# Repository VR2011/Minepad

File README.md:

A macropad to play Minecraft with!

# Features
Not much; it has 11 keys that are binded to the following keys: Esc, F3, E, Q, T, W, A, S, D, Space, Tab

# Schematic

# PCB

# CAD

# Bill of Materials
- 4x M3x5mx4mm heatset inserts
- 1x Seeedxiao RP2040 Microcontroller
- 11x MX-Style Switches
- 4x M3x16mm SHCS Bolt
- 11x White blank DSA keycaps
- 1x PCB
- 2x 3D Printed Case (Top and Bottom Parts)

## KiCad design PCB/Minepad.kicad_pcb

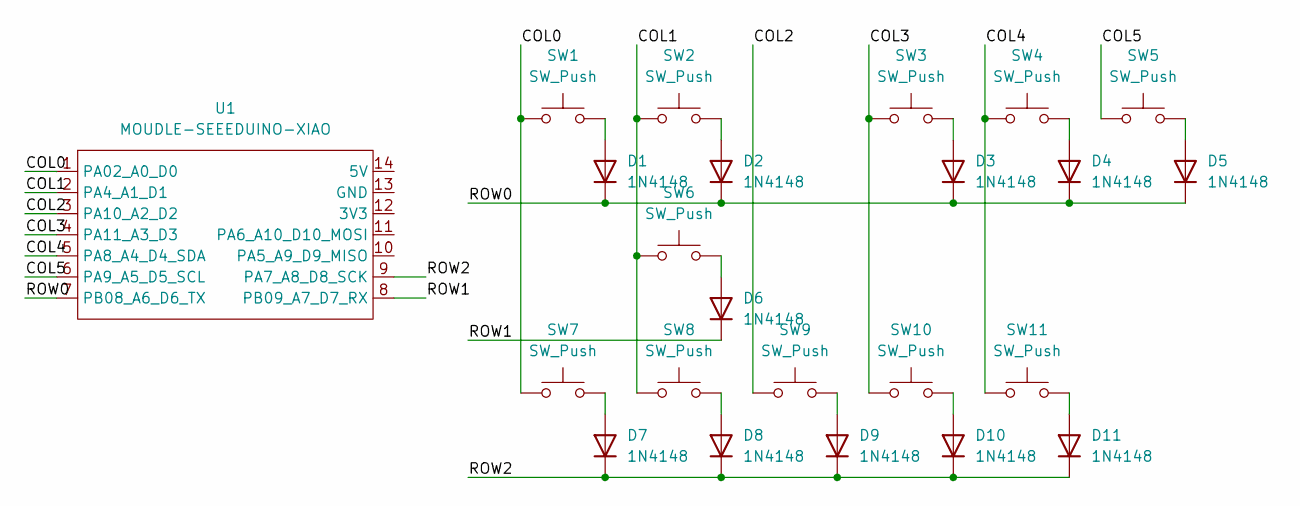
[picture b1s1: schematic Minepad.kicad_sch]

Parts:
D1, D2, D3, D4, D5, D6, D7, D8, D9, D10, D11: 1N4148; D_DO-35_SOD27_P7.62mm_Horizontal
SW1, SW2, SW3, SW4, SW5, SW6, SW7, SW8, SW9, SW10, SW11: SW_Push; SW_Cherry_MX_1.00u_PCB
U1: MOUDLE-SEEEDUINO-XIAO; XIAO-Generic-Hybrid-14P-2.54-21X17.8MM

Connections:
/COL0: SW1.1, SW7.1, U1.1 (PA02_A0_D0)
/COL1: SW2.1, SW6.1, SW8.1, U1.2 (PA4_A1_D1)
/COL2: SW9.1, U1.3 (PA10_A2_D2)
/COL3: SW3.1, SW10.1, U1.4 (PA11_A3_D3)
/COL4: SW4.1, SW11.1, U1.5 (PA8_A4_D4_SDA)
/COL5: SW5.1, U1.6 (PA9_A5_D5_SCL)
/ROW0: D1.1 (K), D2.1 (K), D3.1 (K), D4.1 (K), D5.1 (K), U1.7 (PB08_A6_D6_TX)
/ROW1: D6.1 (K), U1.8 (PB09_A7_D7_RX)
/ROW2: D7.1 (K), D8.1 (K), D9.1 (K), D10.1 (K), D11.1 (K), U1.9 (PA7_A8_D8_SCK)
unnamed: D1.2 (A), SW1.2
unnamed: D2.2 (A), SW2.2
unnamed: D3.2 (A), SW3.2
unnamed: D4.2 (A), SW4.2
unnamed: D5.2 (A), SW5.2
unnamed: D6.2 (A), SW6.2
unnamed: D7.2 (A), SW7.2
unnamed: D8.2 (A), SW8.2
unnamed: D9.2 (A), SW9.2
unnamed: D10.2 (A), SW10.2
unnamed: D11.2 (A), SW11.2

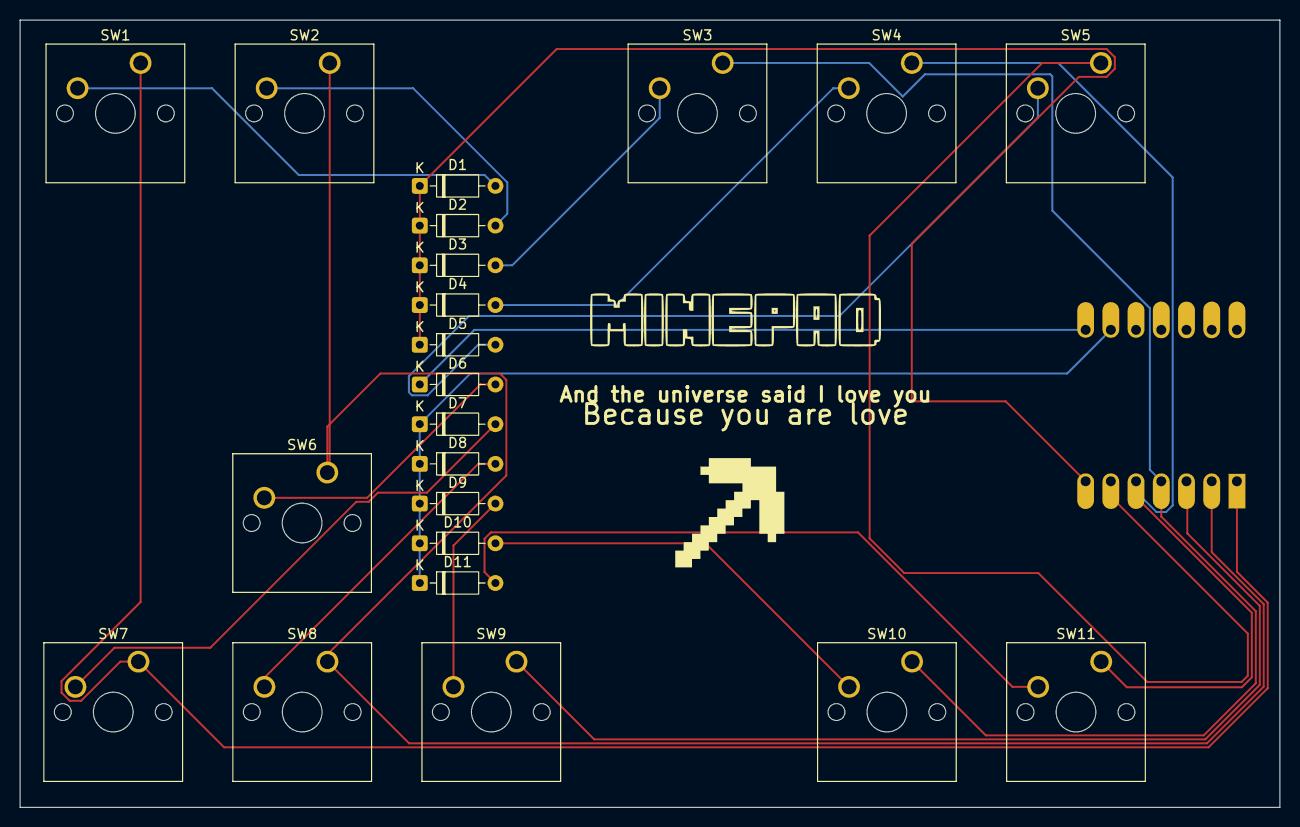
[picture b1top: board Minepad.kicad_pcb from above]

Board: 2 copper layers, 126.9 x 79.3 mm, 23 parts (1 on the bottom side), 20 nets.

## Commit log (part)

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2026-06-30 add files
2026-06-30 added bom
2026-06-30 added readme
2026-06-30 fixed format
2026-06-30 features list update
2026-06-30 fixed bom
